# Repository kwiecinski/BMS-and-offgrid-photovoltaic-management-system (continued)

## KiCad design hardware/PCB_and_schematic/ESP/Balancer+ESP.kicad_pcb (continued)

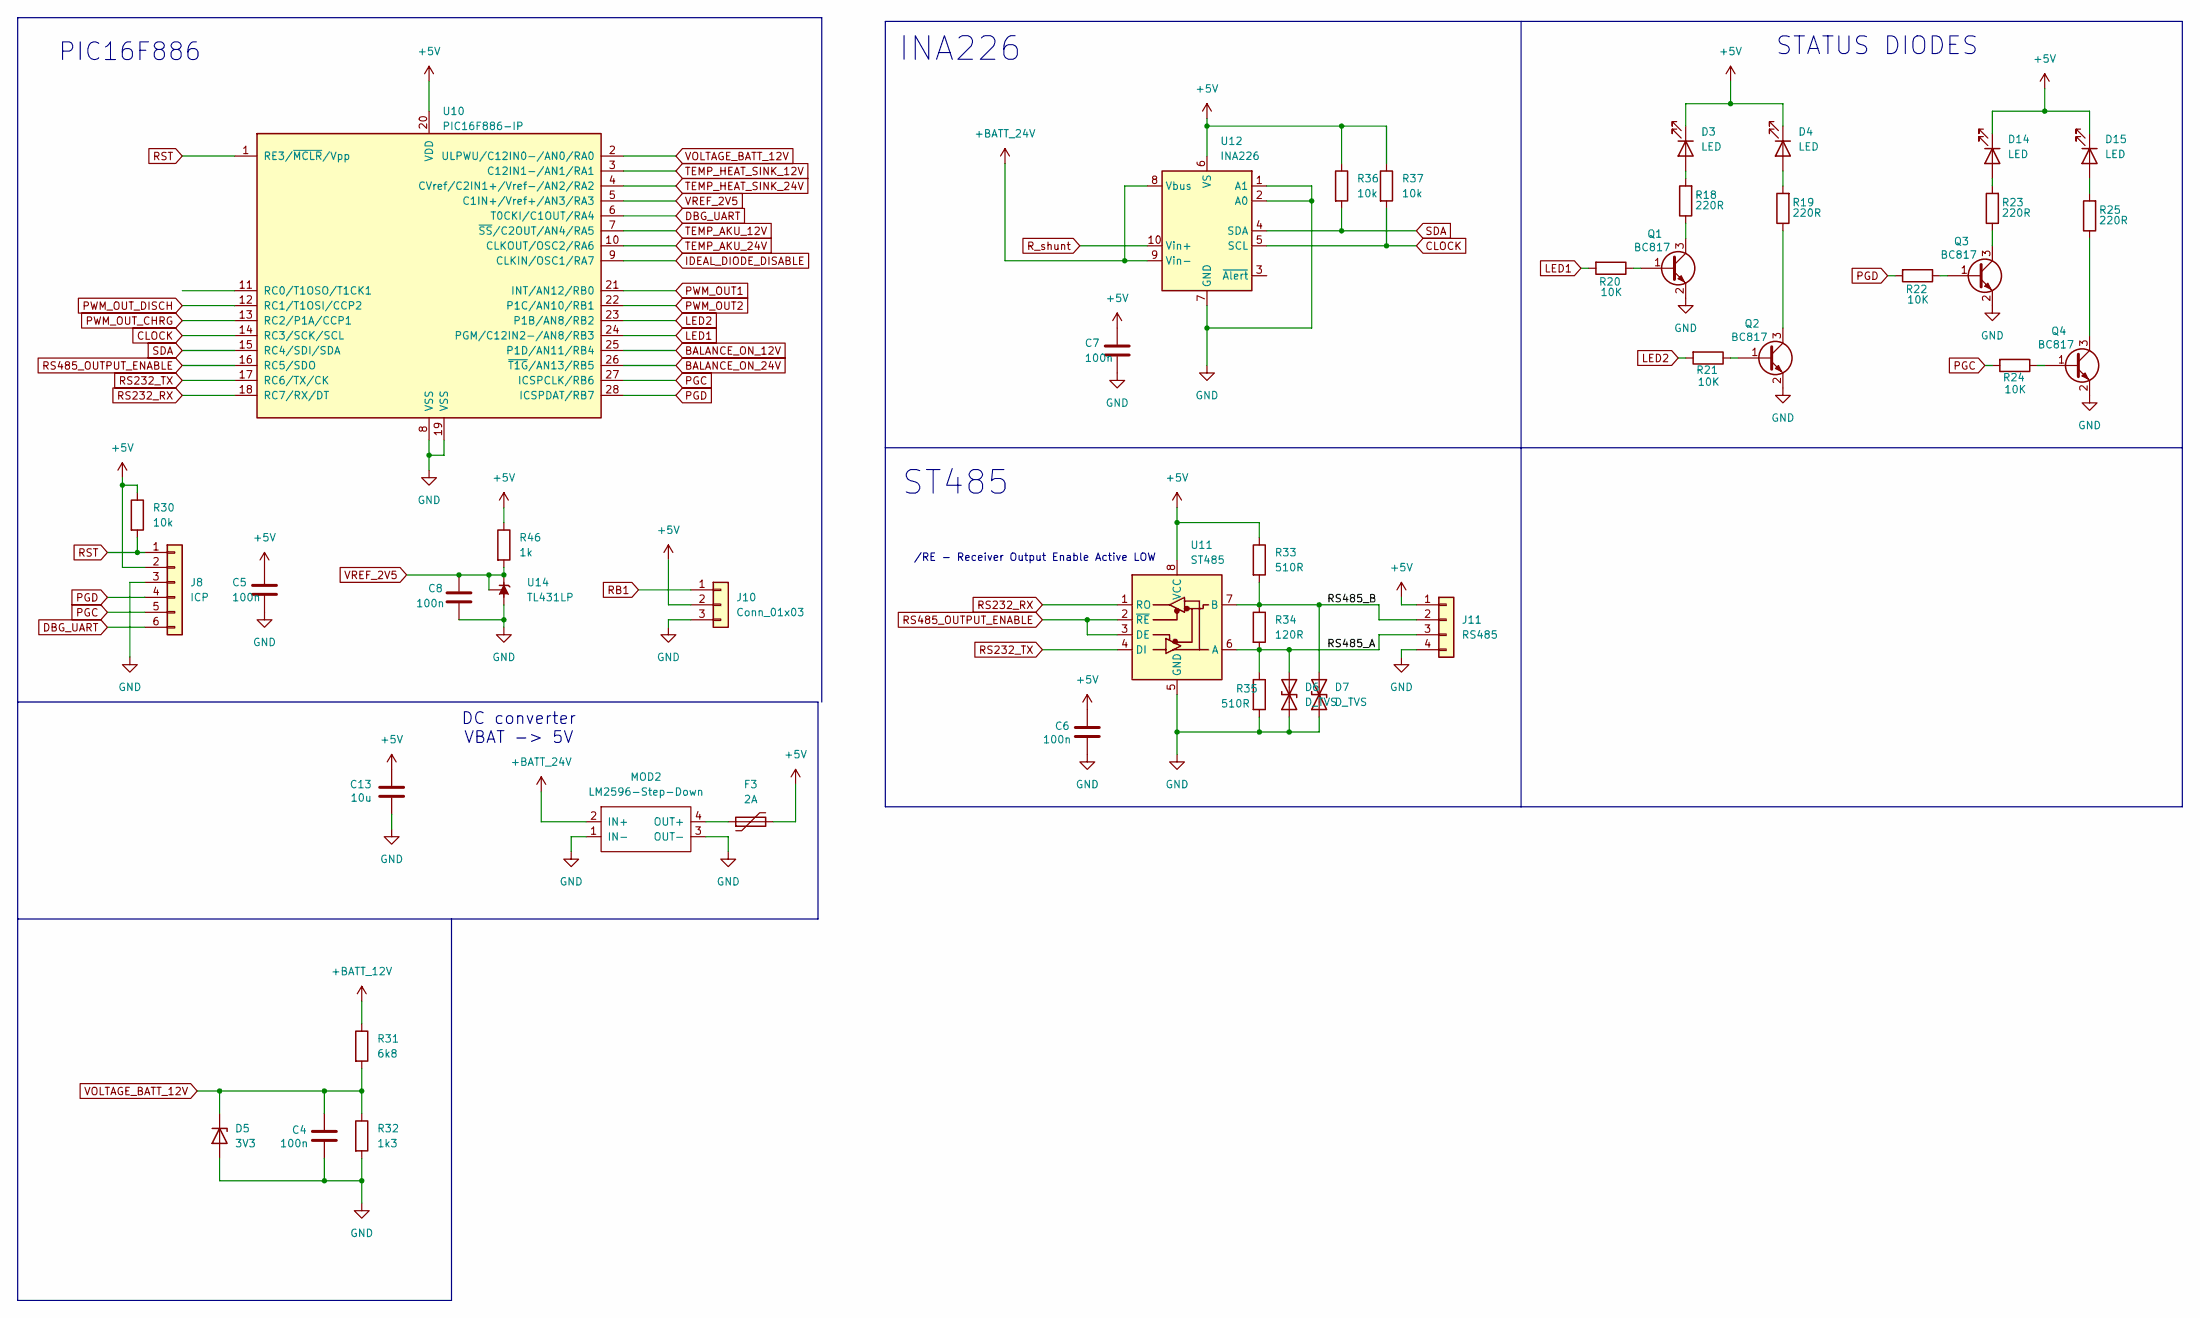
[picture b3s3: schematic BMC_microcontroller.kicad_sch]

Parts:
C4, C5, C6, C8: 100n; C_0805_2012Metric_Pad1.18x1.45mm_HandSolder
C7: 100n; R_0805_2012Metric_Pad1.20x1.40mm_HandSolder
C13: 10u; CP_Elec_6.3x4.5
D3, D4, D14, D15: LED; LED_D5.0mm
D5: 3V3; D_MiniMELF
D6, D7: D_TVS; D_SMC
F3: 2A; Fuse_2512_6332Metric_Pad1.52x3.35mm_HandSolder
J8: ICP; PinHeader_1x06_P2.54mm_Vertical
J10: Conn_01x03; PinHeader_1x03_P2.54mm_Vertical
J11: RS485; PinHeader_1x04_P2.54mm_Vertical
MOD2: LM2596-Step-Down; MP1504_Mini_3A_Step_Down_Conv
Q1, Q2, Q3, Q4: BC817; SOT-23
R18, R19, R23, R25: 220R; R_0805_2012Metric_Pad1.20x1.40mm_HandSolder
R20, R21, R22, R24: 10K; R_0805_2012Metric_Pad1.20x1.40mm_HandSolder
R30, R36, R37: 10k; R_0805_2012Metric_Pad1.20x1.40mm_HandSolder
R31: 6k8; R_0805_2012Metric_Pad1.20x1.40mm_HandSolder
R32: 1k3; R_0805_2012Metric_Pad1.20x1.40mm_HandSolder
R33, R35: 510R; R_0805_2012Metric_Pad1.20x1.40mm_HandSolder
R34: 120R; R_0805_2012Metric_Pad1.20x1.40mm_HandSolder
R46: 1k; R_0805_2012Metric_Pad1.20x1.40mm_HandSolder
U10: PIC16F886-IP; SOIC-28W_7.5x17.9mm_P1.27mm
U11: ST485; SOIC-8_3.9x4.9mm_P1.27mm
U12: INA226; VSSOP-10_3x3mm_P0.5mm
U14: TL431LP; TO-92_Inline

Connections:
+5V: C5.1, C6.1, C7.1, C13.2, D3.1 (K), D4.1 (K), D14.1 (K), D15.1 (K), F3.2, J8.2, J10.2, J11.1, R30.1, R33.1, R36.1, R37.1, R46.1, U10.20 (VDD), U11.8 (VCC), U12.6 (VS); also elsewhere on the board
+BATT_12V: R31.1; also elsewhere on the board
+BATT_24V: MOD2.2 (IN+), U12.8 (Vbus), U12.9 (Vin-); also elsewhere on the board
/BMS/BMS_microcontroller/RS485_A: D6.2 (A2), J11.3, R34.2, R35.1, U11.6 (A)
/BMS/BMS_microcontroller/RS485_B: D7.2 (A2), J11.2, R33.2, R34.1, U11.7 (B)
BALANCE_ON_12V: U10.25 (P1D/AN11/RB4); also elsewhere on the board
BALANCE_ON_24V: U10.26 (~T1G/AN13/RB5); also elsewhere on the board
CLOCK: R37.2, U10.14 (RC3/SCK/SCL), U12.5 (SCL)
DBG_UART: J8.6, U10.6 (T0CKI/C1OUT/RA4)
GND: C4.2, C5.2, C6.2, C7.2, C8.2, C13.1, D5.2 (A), D6.1 (A1), D7.1 (A1), J8.3, J10.3, J11.4, MOD2.1 (IN-), MOD2.3 (OUT-), Q1.2 (E), Q2.2 (E), Q3.2 (E), Q4.2 (E), R32.2, R35.2, U10.8 (VSS), U10.19 (VSS), U11.5 (GND), U12.1 (A1), U12.2 (A0), U12.7 (GND), U14.2 (A); also elsewhere on the board
IDEAL_DIODE_DISABLE: U10.9 (CLKIN/OSC1/RA7)
LED1: R20.2, U10.24 (PGM/C12IN2-/AN8/RB3)
LED2: R21.2, U10.23 (P1B/AN8/RB2)
unnamed: D3.2 (A), R18.2
unnamed: D4.2 (A), R19.2
unnamed: D14.2 (A), R23.2
unnamed: D15.2 (A), R25.2
unnamed: F3.1, MOD2.4 (OUT+)
unnamed: Q1.1 (B), R20.1
unnamed: Q1.3 (C), R18.1
unnamed: Q2.1 (B), R21.1
unnamed: Q2.3 (C), R19.1
unnamed: Q3.1 (B), R22.1
unnamed: Q3.3 (C), R23.1
unnamed: Q4.1 (B), R24.1
unnamed: Q4.3 (C), R25.1
PGC: J8.5, R24.2, U10.27 (ICSPCLK/RB6)
PGD: J8.4, R22.2, U10.28 (ICSPDAT/RB7)
PWM_OUT1: U10.21 (INT/AN12/RB0); also elsewhere on the board
PWM_OUT2: U10.22 (P1C/AN10/RB1); also elsewhere on the board
PWM_OUT_CHRG: U10.13 (RC2/P1A/CCP1); also elsewhere on the board
PWM_OUT_DISCH: U10.12 (RC1/T1OSI/CCP2); also elsewhere on the board
RB1: J10.1
RS232_RX: U10.18 (RC7/RX/DT), U11.1 (RO)
RS232_TX: U10.17 (RC6/TX/CK), U11.4 (DI)
RS485_OUTPUT_ENABLE: U10.16 (RC5/SDO), U11.2 (~RE), U11.3 (DE)
RST: J8.1, R30.2, U10.1 (RE3/~MCLR/Vpp)
R_shunt: U12.10 (Vin+); also elsewhere on the board
SDA: R36.2, U10.15 (RC4/SDI/SDA), U12.4 (SDA)
TEMP_AKU_12V: U10.7 (~SS/C2OUT/AN4/RA5); also elsewhere on the board
TEMP_AKU_24V: U10.10 (CLKOUT/OSC2/RA6); also elsewhere on the board
TEMP_HEAT_SINK_12V: U10.3 (C12IN1-/AN1/RA1); also elsewhere on the board
TEMP_HEAT_SINK_24V: U10.4 (CVref/C2IN1+/Vref-/AN2/RA2); also elsewhere on the board
VOLTAGE_BATT_12V: C4.1, D5.1 (K), R31.2, R32.1, U10.2 (ULPWU/C12IN0-/AN0/RA0)
VREF_2V5: C8.1, R46.2, U10.5 (C1IN+/Vref+/AN3/RA3), U14.1 (REF), U14.3 (K)

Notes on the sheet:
INA226
PIC16F886
ST485
DC converter VBAT -> 5V
/RE - Receiver Output Enable Active LOW
STATUS DIODES

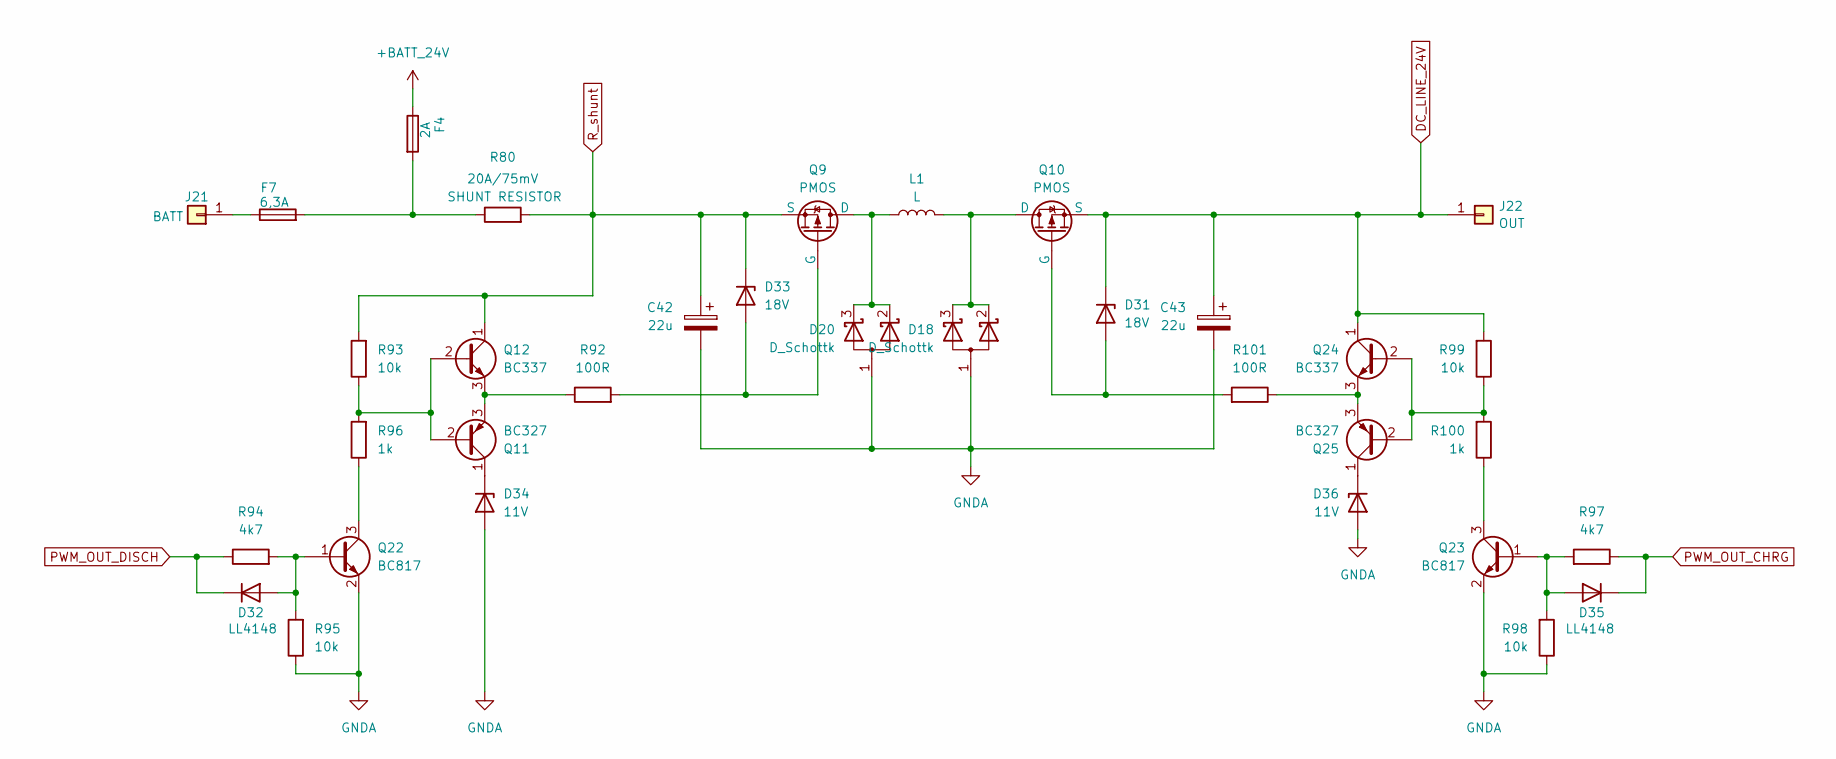
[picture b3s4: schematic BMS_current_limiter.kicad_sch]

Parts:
C42, C43: 22u; CP_EIA-3528-21_Kemet-B
D18, D20: D_Schottk; TO-220-3_Vertical
D31, D33: 18V; D_MiniMELF
D32, D35: LL4148; D_MiniMELF
D34, D36: 11V; D_MiniMELF
F4: 2A; Fuse_2512_6332Metric_Pad1.52x3.35mm_HandSolder
F7: 6,3A; Fuse_2512_6332Metric_Pad1.52x3.35mm_HandSolder
J21: BATT; Pin_D1.4mm_L8.5mm_W2.8mm_FlatFork
J22: OUT; Pin_D1.4mm_L8.5mm_W2.8mm_FlatFork
L1: L; L_Axial_L26.0mm_D11.0mm_P30.48mm_Horizontal_Fastron_77A
Q9, Q10: PMOS; TO-220-3_Vertical
Q11, Q25: BC327; TO-92_Inline
Q12, Q24: BC337; TO-92_Inline
Q22, Q23: BC817; SOT-23
R80: 20A/75mV; R_Axial_Power_L38.0mm_W9.0mm_P40.64mm
R92, R101: 100R; R_0805_2012Metric
R93, R95, R98, R99: 10k; R_0805_2012Metric
R94, R97: 4k7; R_0805_2012Metric
R96, R100: 1k; R_0805_2012Metric

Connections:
+BATT_24V: F4.1; also elsewhere on the board
DC_LINE_24V: C43.1, D31.1 (K), J22.1, Q10.3 (S), Q24.1 (C), R99.2
GNDA: C42.2, C43.2, D18.1 (A), D20.1 (A), D34.2 (A), D36.2 (A), Q22.2 (E), Q23.2 (E), R95.1, R98.1; also elsewhere on the board
unnamed: D31.2 (A), Q10.2 (G), R101.2
unnamed: D32.2 (A), Q22.1 (B), R94.2, R95.2
unnamed: D33.2 (A), Q9.2 (G), R92.2
unnamed: D34.1 (K), Q11.1 (C)
unnamed: D35.2 (A), Q23.1 (B), R97.2, R98.2
unnamed: D36.1 (K), Q25.1 (C)
unnamed: F4.2, F7.2, R80.1
unnamed: F7.1, J21.1
unnamed: D20.2 (K), D20.3 (K), L1.1, Q9.1 (D)
unnamed: D18.2 (K), D18.3 (K), L1.2, Q10.1 (D)
unnamed: Q11.2 (B), Q12.2 (B), R93.1, R96.2
unnamed: Q11.3 (E), Q12.3 (E), R92.1
unnamed: Q22.3 (C), R96.1
unnamed: Q23.3 (C), R100.1
unnamed: Q24.2 (B), Q25.2 (B), R99.1, R100.2
unnamed: Q24.3 (E), Q25.3 (E), R101.1
PWM_OUT_CHRG: D35.1 (K), R97.1; also elsewhere on the board
PWM_OUT_DISCH: D32.1 (K), R94.1; also elsewhere on the board
R_shunt: C42.1, D33.1 (K), Q9.3 (S), Q12.1 (C), R80.2, R93.2; also elsewhere on the board

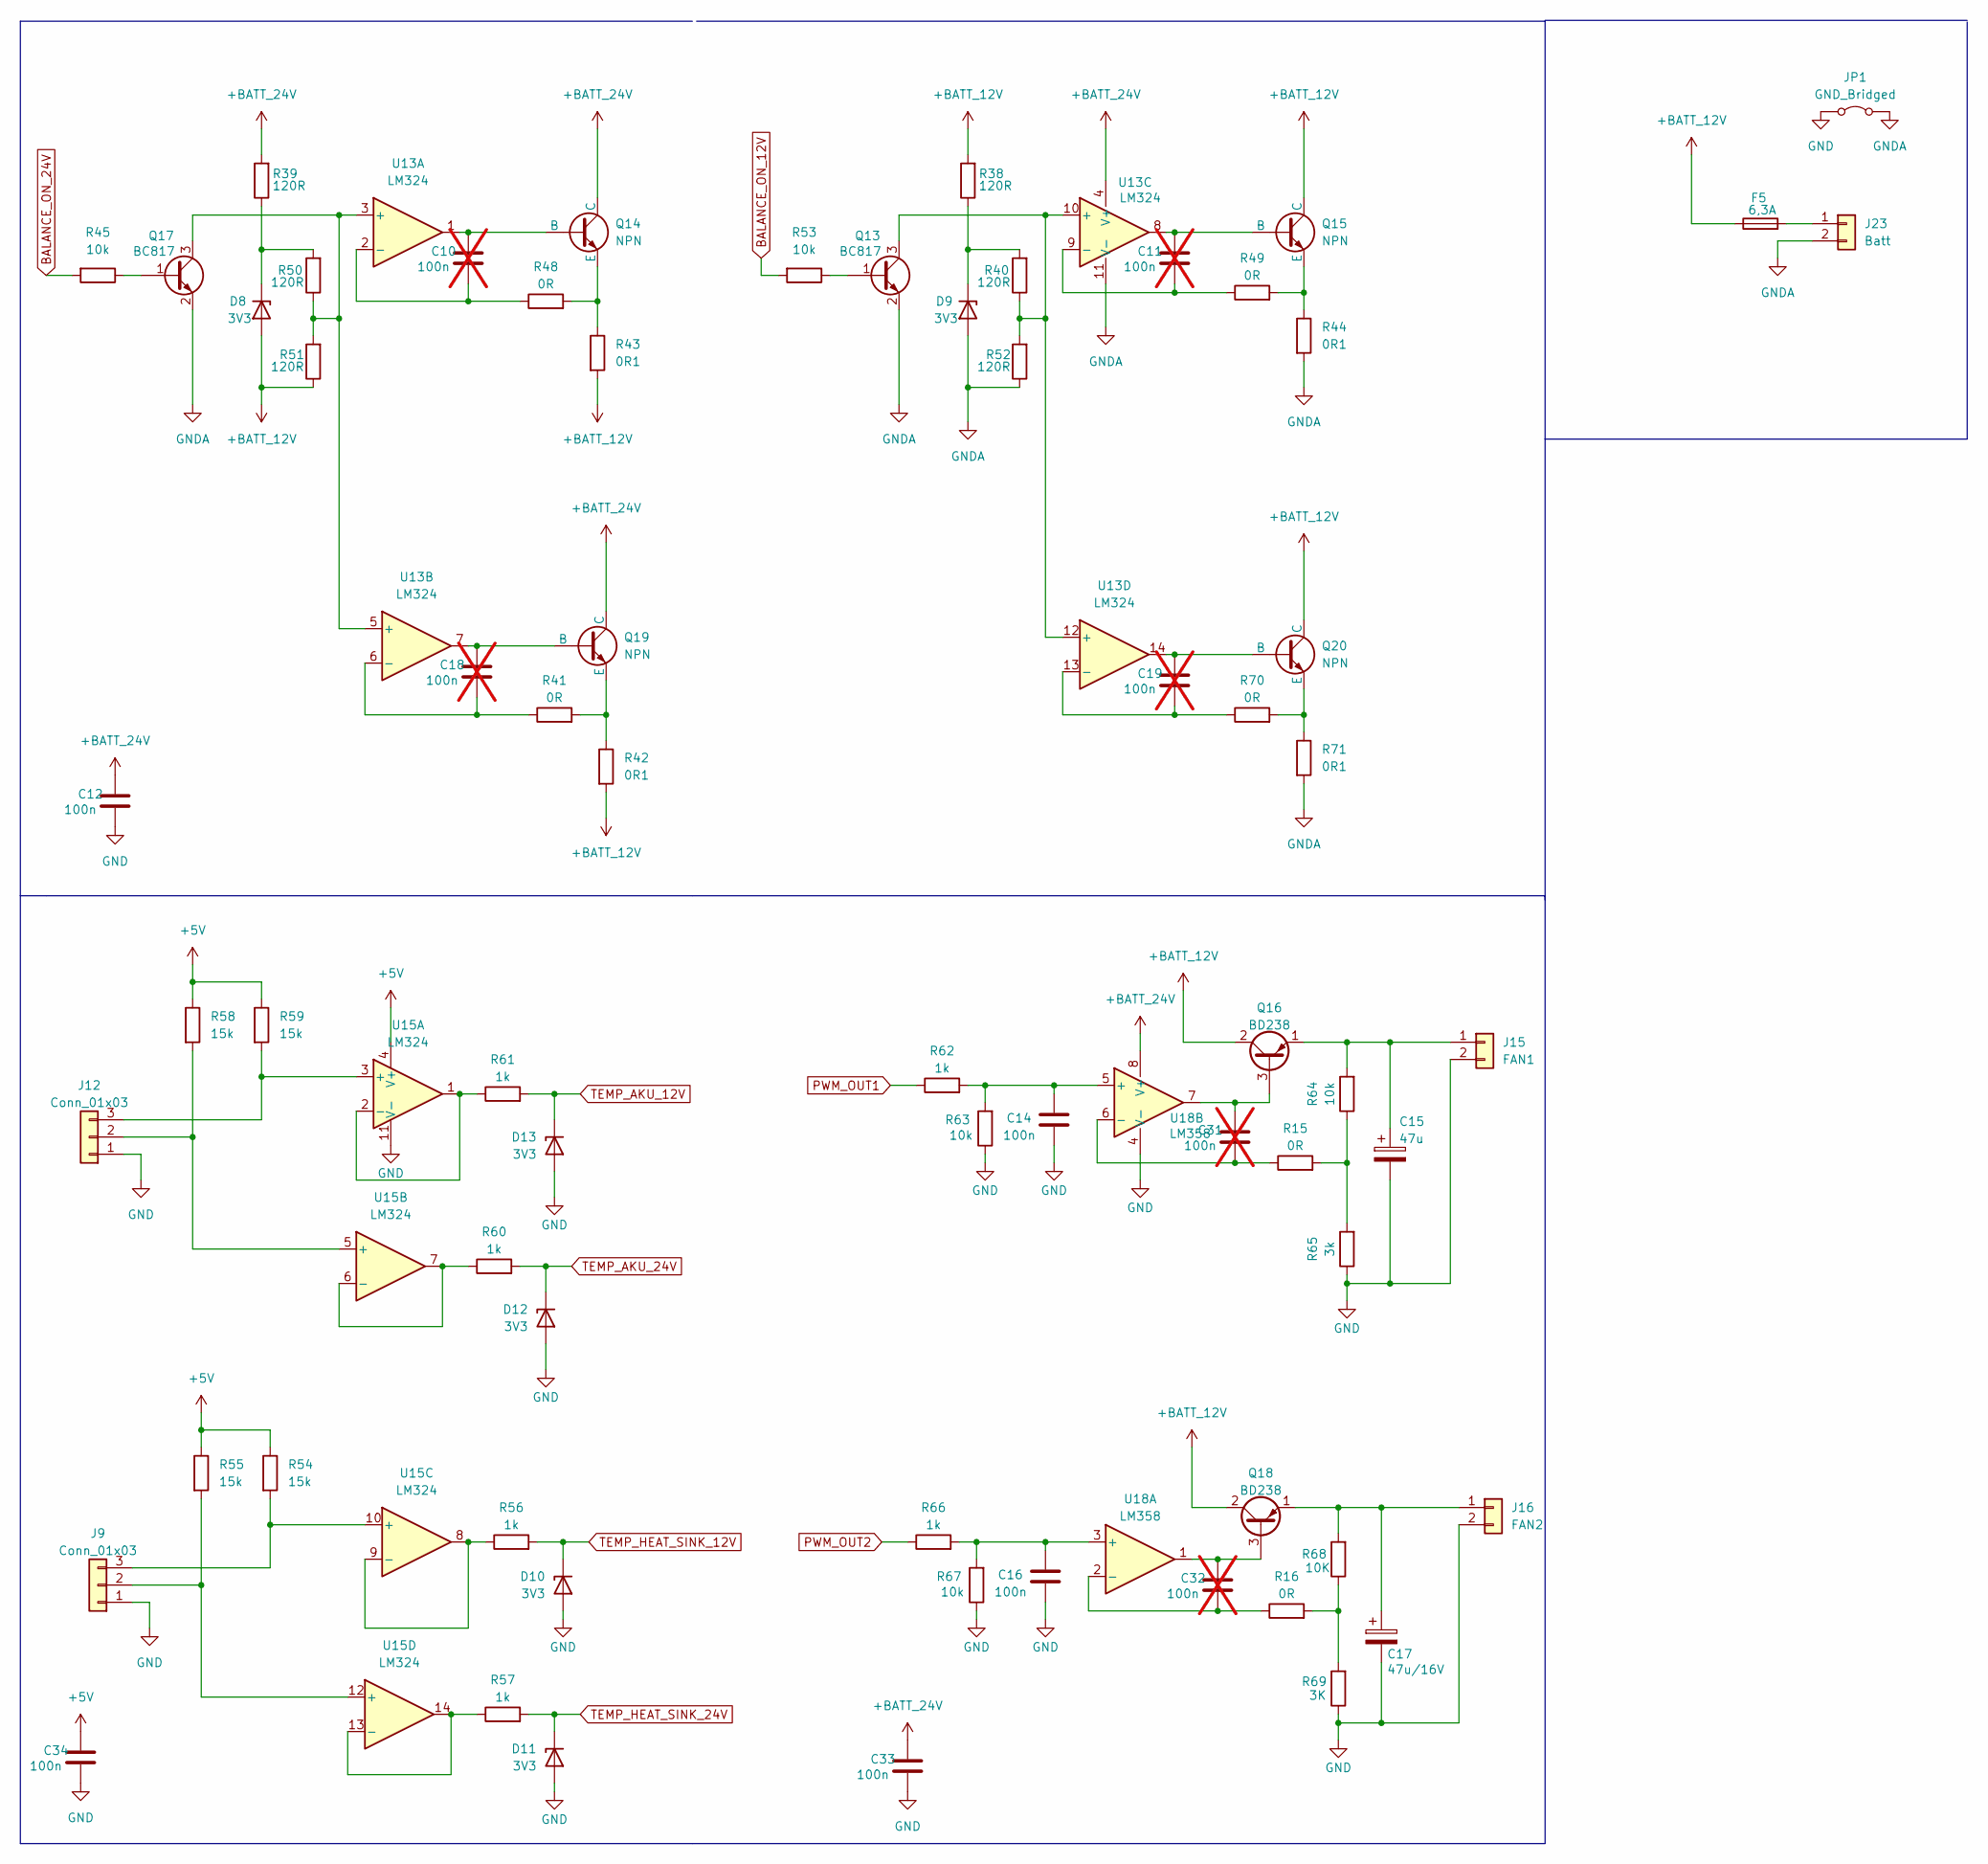
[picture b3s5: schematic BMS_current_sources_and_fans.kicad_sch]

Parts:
C10, C11, C18, C19, C31, C32: 100n; C_0805_2012Metric_Pad1.18x1.45mm_HandSolder; not fitted
C12, C14, C16, C33, C34: 100n; C_0805_2012Metric_Pad1.18x1.45mm_HandSolder
C15: 47u; CP_Radial_D5.0mm_P2.00mm
C17: 47u/16V; CP_Radial_D5.0mm_P2.00mm
D8, D9, D10, D11, D12, D13: 3V3; D_MiniMELF
F5: 6,3A; Fuse_2512_6332Metric_Pad1.52x3.35mm_HandSolder
J9, J12: Conn_01x03; JST_EH_B3B-EH-A_1x03_P2.50mm_Vertical
J15: FAN1; JST_EH_B2B-EH-A_1x02_P2.50mm_Vertical
J16: FAN2; JST_EH_B2B-EH-A_1x02_P2.50mm_Vertical
J23: Batt; PinHeader_1x02_P2.54mm_Vertical
JP1: GND_Bridged; SolderJumper-2_P1.3mm_Bridged2Bar_Pad1.0x1.5mm
Q13, Q17: BC817; SOT-23
Q14, Q15, Q19, Q20: NPN; TO-220-3_Vertical
Q16, Q18: BD238; TO-126-3_Vertical
R15, R16, R41, R48, R49, R70: 0R; R_0805_2012Metric_Pad1.20x1.40mm_HandSolder
R38, R39, R40, R50, R51, R52: 120R; R_0805_2012Metric_Pad1.20x1.40mm_HandSolder
R42, R43, R44, R71: 0R1; R_0805_2012Metric_Pad1.20x1.40mm_HandSolder
R45, R53, R63, R64, R67: 10k; R_0805_2012Metric_Pad1.20x1.40mm_HandSolder
R54, R55, R58, R59: 15k; R_0805_2012Metric_Pad1.20x1.40mm_HandSolder
R56, R57, R60, R61, R62, R66: 1k; R_0805_2012Metric_Pad1.20x1.40mm_HandSolder
R65: 3k; R_0805_2012Metric_Pad1.20x1.40mm_HandSolder
R68: 10K; R_0805_2012Metric_Pad1.20x1.40mm_HandSolder
R69: 3K; R_0805_2012Metric_Pad1.20x1.40mm_HandSolder
U13, U15: LM324; SOIC-14_3.9x8.7mm_P1.27mm
U18: LM358; SO-8_3.9x4.9mm_P1.27mm

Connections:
+5V: C34.1, R54.1, R55.1, R58.1, R59.1, U15.4 (V+); also elsewhere on the board
+BATT_12V: D8.2 (A), F5.1, Q15.1 (C), Q16.2 (C), Q18.2 (C), Q20.1 (C), R38.2, R42.2, R43.2, R51.1; also elsewhere on the board
+BATT_24V: C12.1, C33.1, Q14.1 (C), Q19.1 (C), R39.2, U13.4 (V+), U18.8 (V+); also elsewhere on the board
BALANCE_ON_12V: R53.2; also elsewhere on the board
BALANCE_ON_24V: R45.2; also elsewhere on the board
GND: C12.2, C14.2, C15.2, C16.2, C17.2, C33.2, C34.2, D10.2 (A), D11.2 (A), D12.2 (A), D13.2 (A), J9.1, J12.1, J15.2, J16.2, JP1.1 (A), R63.1, R65.1, R67.1, R69.1, U15.11 (V-), U18.4 (V-); also elsewhere on the board
GNDA: D9.2 (A), J23.2, JP1.2 (B), Q13.2 (E), Q17.2 (E), R44.2, R52.1, R71.2, U13.11 (V-); also elsewhere on the board
unnamed: D8.1 (K), R39.1, R50.2
unnamed: D9.1 (K), R38.1, R40.2
unnamed: J9.2, R55.2, U15.12 (+)
unnamed: J9.3, R54.2, U15.10 (+)
unnamed: J12.2, R58.2, U15.5 (+)
unnamed: J12.3, R59.2, U15.3 (+)
unnamed: C15.1, J15.1, Q16.1 (E), R64.2
unnamed: C17.1, J16.1, Q18.1 (E), R68.2
unnamed: F5.2, J23.1
unnamed: Q13.1 (B), R53.1
unnamed: Q13.3 (C), R40.1, R52.2, U13.10 (+), U13.12 (+)
unnamed: C10.1, Q14.2 (B), U13.1
unnamed: Q14.3 (E), R43.1, R48.2
unnamed: C11.1, Q15.2 (B), U13.8
unnamed: Q15.3 (E), R44.1, R49.2
unnamed: C31.1, Q16.3 (B), U18.7
unnamed: Q17.1 (B), R45.1
unnamed: Q17.3 (C), R50.1, R51.2, U13.3 (+), U13.5 (+)
unnamed: C32.1, Q18.3 (B), U18.1
unnamed: C18.1, Q19.2 (B), U13.7
unnamed: Q19.3 (E), R41.2, R42.1
unnamed: C19.1, Q20.2 (B), U13.14
unnamed: Q20.3 (E), R70.2, R71.1
unnamed: R15.2, R64.1, R65.2
unnamed: R16.2, R68.1, R69.2
unnamed: C10.2, R48.1, U13.2 (-)
unnamed: C18.2, R41.1, U13.6 (-)
unnamed: C11.2, R49.1, U13.9 (-)
unnamed: C19.2, R70.1, U13.13 (-)
unnamed: R61.1, U15.1, U15.2 (-)
unnamed: R60.1, U15.6 (-), U15.7
unnamed: R56.1, U15.8, U15.9 (-)
unnamed: R57.1, U15.13 (-), U15.14
unnamed: C16.1, R66.2, R67.2, U18.3 (+)
unnamed: C32.2, R16.1, U18.2 (-)
unnamed: C14.1, R62.2, R63.2, U18.5 (+)
unnamed: C31.2, R15.1, U18.6 (-)
PWM_OUT1: R62.1; also elsewhere on the board
PWM_OUT2: R66.1; also elsewhere on the board
TEMP_AKU_12V: D13.1 (K), R61.2; also elsewhere on the board
TEMP_AKU_24V: D12.1 (K), R60.2; also elsewhere on the board
TEMP_HEAT_SINK_12V: D10.1 (K), R56.2; also elsewhere on the board
TEMP_HEAT_SINK_24V: D11.1 (K), R57.2; also elsewhere on the board

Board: 2 copper layers, 253 parts (13 on the bottom side), 172 nets, no tracks yet.
